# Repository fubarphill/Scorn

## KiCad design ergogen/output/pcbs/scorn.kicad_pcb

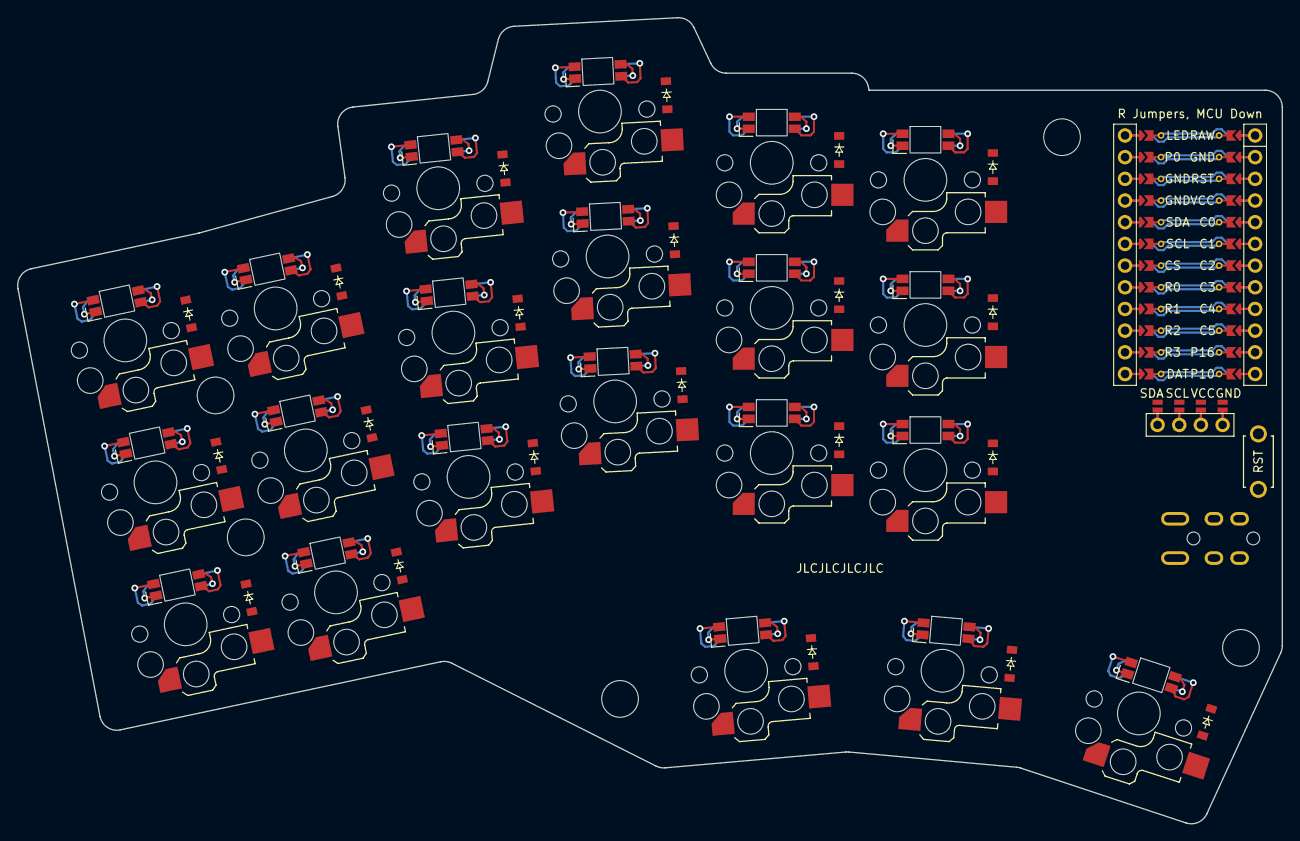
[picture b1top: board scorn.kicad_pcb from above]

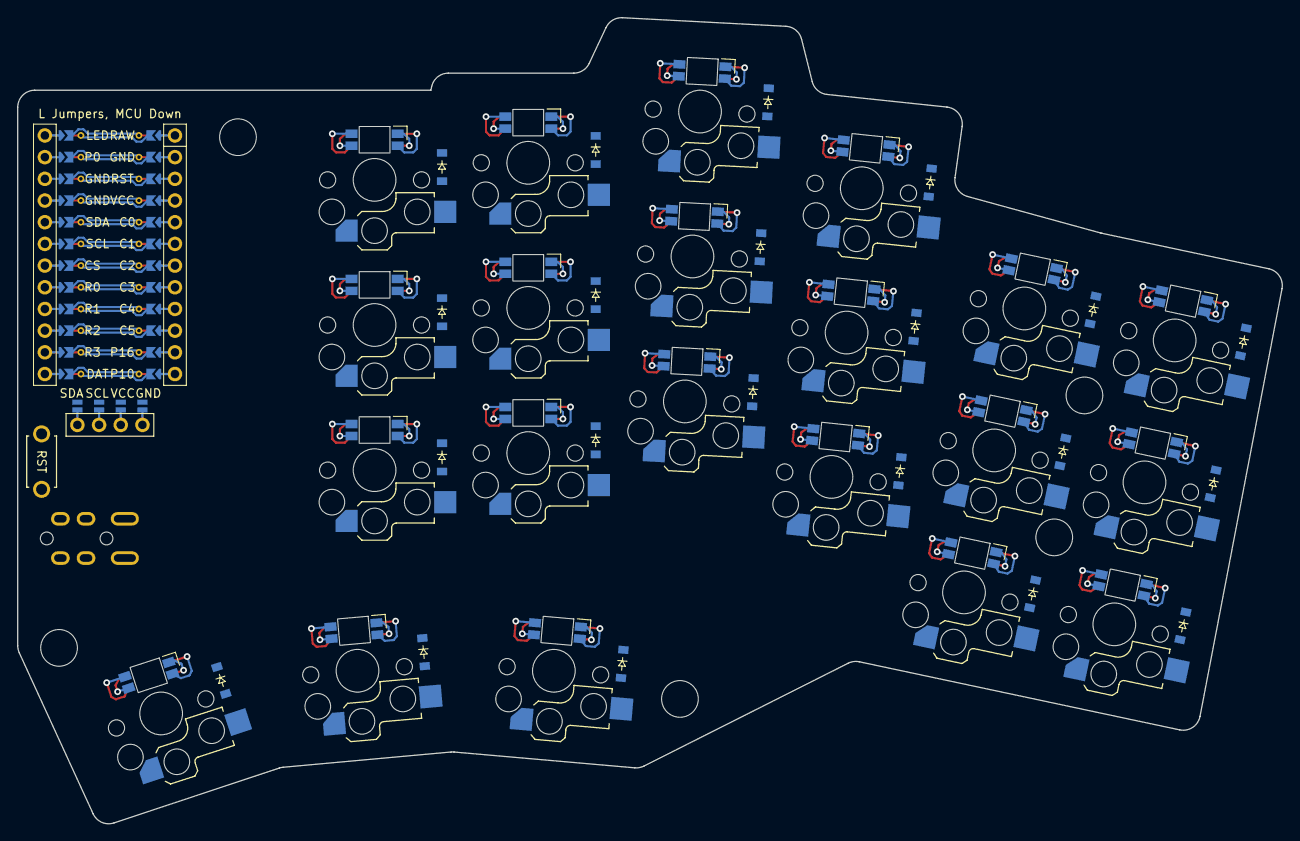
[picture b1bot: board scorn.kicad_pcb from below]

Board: 2 copper layers, 148.1 x 94.4 mm, 93 parts (63 on the bottom side), 62 nets.

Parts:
D1, D2, D3, D4, D5, D6, D7, D8, D9, D10, D11, D12, D13, D14, D15, D16, D17, D18, D19, D20, D21, D22, D23, D24, D25, D26, D27, D28, D29, D30, D31, D32, D33, D34, D35, D36, D37, D38, D39, D40, D41, D42: diode_tht_sod123
DISP1: display_ssd1306
LED1, LED2, LED3, LED4, LED5, LED6, LED7, LED8, LED9, LED10, LED11, LED12, LED13, LED14, LED15, LED16, LED17, LED18, LED19, LED20, LED21: led_SK6812mini-e (per-key, reversible)
MCU1: mcu_nice_nano
MH1, MH2, MH3, MH4, MH5: mounting_hole_npth
RST1: reset_switch_tht_top
SW1, SW2, SW3, SW4, SW5, SW6, SW7, SW8, SW9, SW10, SW11, SW12, SW13, SW14, SW15, SW16, SW17, SW18, SW19, SW20, SW21: switch_choc_v1_v2
TRRS1: trrs_pj320a (reversible, symmetric)

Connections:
C0: MCU1.120, SW1.1, SW2.1, SW3.1
C1: MCU1.119, SW4.1, SW5.1, SW6.1
C2: MCU1.118, SW7.1, SW8.1, SW9.1
C3: MCU1.117, SW10.1, SW11.1, SW12.1, SW19.1
C4: MCU1.116, SW13.1, SW14.1, SW15.1, SW20.1
C5: MCU1.115, SW16.1, SW17.1, SW18.1, SW21.1
DAT: MCU1.112, TRRS1.3
DISP1_1: DISP1.1, DISP1.10, DISP1.23
DISP1_2: DISP1.2, DISP1.11, DISP1.22
DISP1_3: DISP1.3, DISP1.12, DISP1.21
DISP1_4: DISP1.4, DISP1.13, DISP1.20
GND: DISP1.14, DISP1.24, LED1.3, LED2.3, LED3.3, LED4.3, LED5.3, LED6.3, LED7.3, LED8.3, LED9.3, LED10.3, LED11.3, LED12.3, LED13.3, LED14.3, LED15.3, LED16.3, LED17.3, LED18.3, LED19.3, LED20.3, LED21.3, MCU1.103, MCU1.104, MCU1.123, RST1.2, TRRS1.2
LED: LED18.4, MCU1.101
LED_1: LED15.4, LED18.2
LED_2: LED12.4, LED15.2
LED_3: LED9.4, LED12.2
LED_4: LED6.4, LED9.2
LED_5: LED3.4, LED6.2
LED_6: LED2.4, LED3.2
LED_7: LED2.2, LED5.4
LED_8: LED5.2, LED8.4
LED_9: LED8.2, LED11.4
LED_10: LED11.2, LED14.4
LED_11: LED14.2, LED17.4
LED_12: LED16.4, LED17.2
LED_13: LED13.4, LED16.2
LED_14: LED10.4, LED13.2
LED_15: LED7.4, LED10.2
LED_16: LED4.4, LED7.2
LED_17: LED1.4, LED4.2
LED_18: LED1.2, LED19.4
LED_19: LED19.2, LED20.4
LED_20: LED20.2, LED21.4
R0: D3.1, D6.1, D9.1, D12.1, D15.1, D18.1, D24.1, D27.1, D30.1, D33.1, D36.1, D39.1, MCU1.108
R1: D2.1, D5.1, D8.1, D11.1, D14.1, D17.1, D23.1, D26.1, D29.1, D32.1, D35.1, D38.1, MCU1.109
R2: D1.1, D4.1, D7.1, D10.1, D13.1, D16.1, D22.1, D25.1, D28.1, D31.1, D34.1, D37.1, MCU1.110
R3: D19.1, D20.1, D21.1, D40.1, D41.1, D42.1, MCU1.111
RST: MCU1.122, RST1.1
SCL: DISP1.16, DISP1.26, MCU1.106
SDA: DISP1.17, DISP1.27, MCU1.105
VCC: DISP1.15, DISP1.25, LED1.1, LED2.1, LED3.1, LED4.1, LED5.1, LED6.1, LED7.1, LED8.1, LED9.1, LED10.1, LED11.1, LED12.1, LED13.1, LED14.1, LED15.1, LED16.1, LED17.1, LED18.1, LED19.1, LED20.1, LED21.1, MCU1.121, TRRS1.4
index_bottom: D13.2, D34.2, SW13.2
index_home: D14.2, D35.2, SW14.2
index_top: D15.2, D36.2, SW15.2
inner_bottom: D16.2, D37.2, SW16.2
inner_cluster: D19.2, D40.2, SW19.2
inner_home: D17.2, D38.2, SW17.2
inner_top: D18.2, D39.2, SW18.2
mid_cluster: D20.2, D41.2, SW20.2
middle_bottom: D10.2, D31.2, SW10.2
middle_home: D11.2, D32.2, SW11.2
middle_top: D12.2, D33.2, SW12.2
outer_bottom: D1.2, D22.2, SW1.2
outer_cluster: D21.2, D42.2, SW21.2
outer_home: D2.2, D23.2, SW2.2
outer_top: D3.2, D24.2, SW3.2
pinky_bottom: D4.2, D25.2, SW4.2
pinky_home: D5.2, D26.2, SW5.2
pinky_top: D6.2, D27.2, SW6.2
ring_bottom: D7.2, D28.2, SW7.2
ring_home: D8.2, D29.2, SW8.2
ring_top: D9.2, D30.2, SW9.2
